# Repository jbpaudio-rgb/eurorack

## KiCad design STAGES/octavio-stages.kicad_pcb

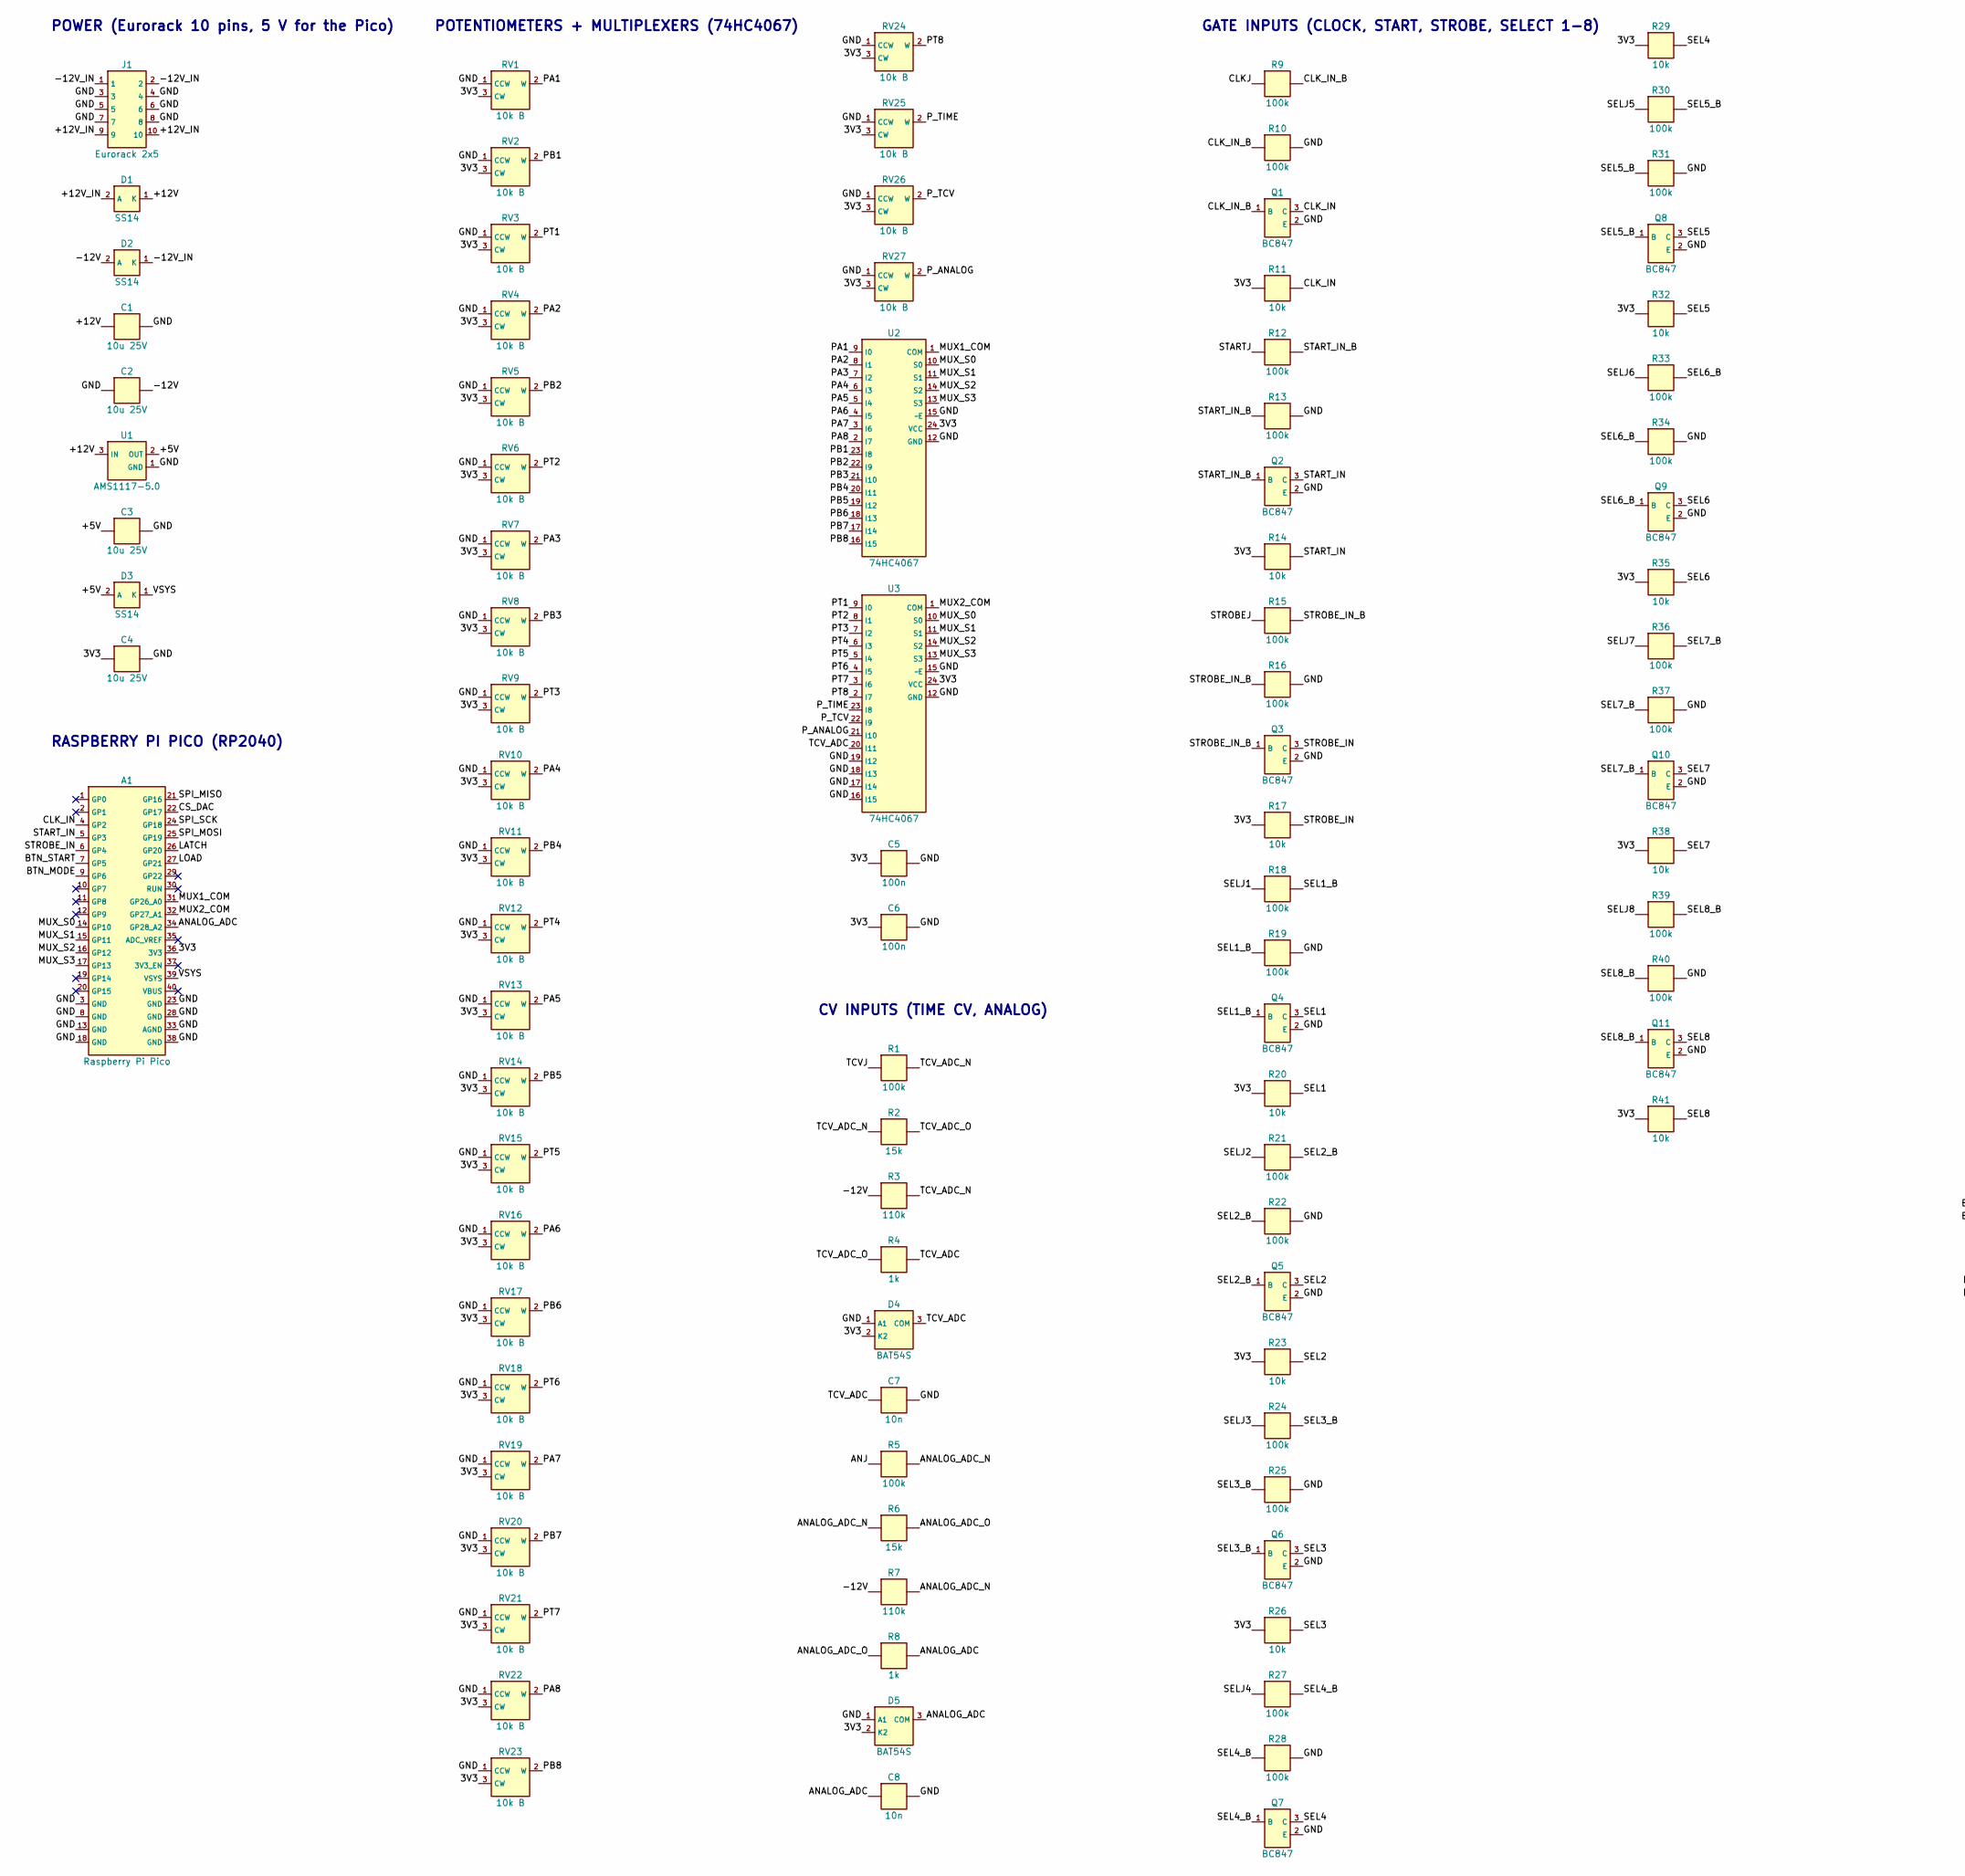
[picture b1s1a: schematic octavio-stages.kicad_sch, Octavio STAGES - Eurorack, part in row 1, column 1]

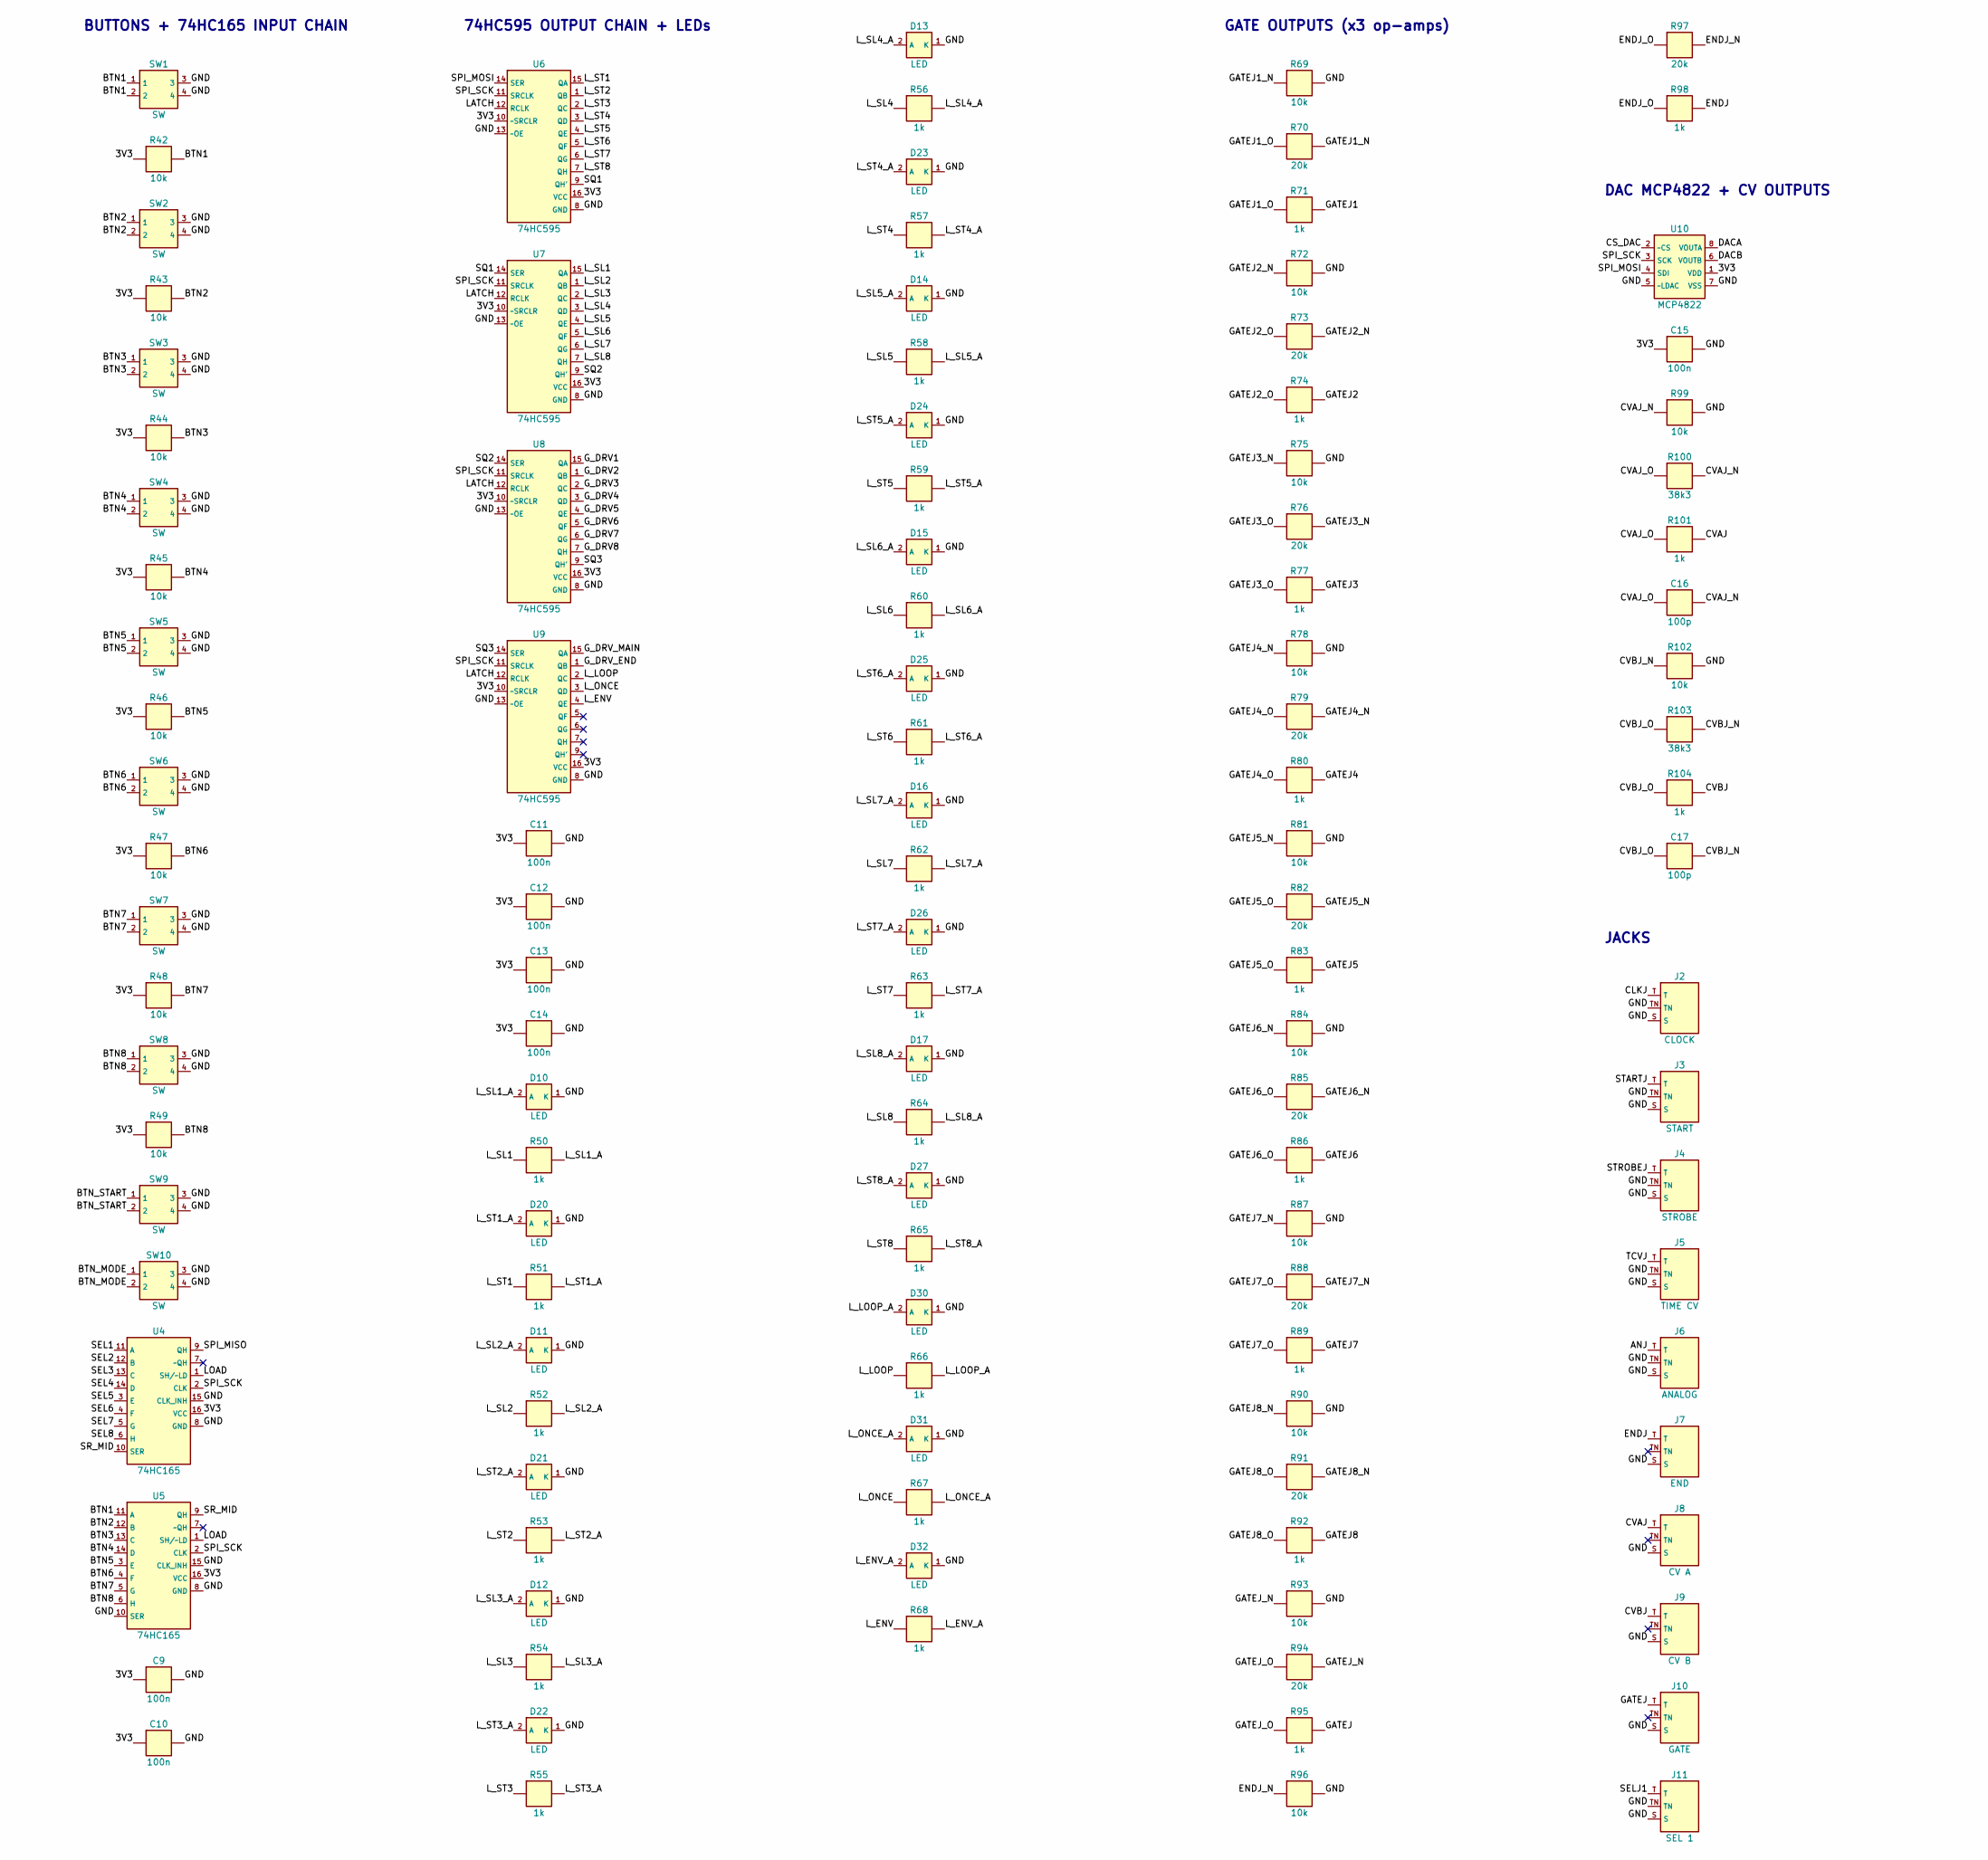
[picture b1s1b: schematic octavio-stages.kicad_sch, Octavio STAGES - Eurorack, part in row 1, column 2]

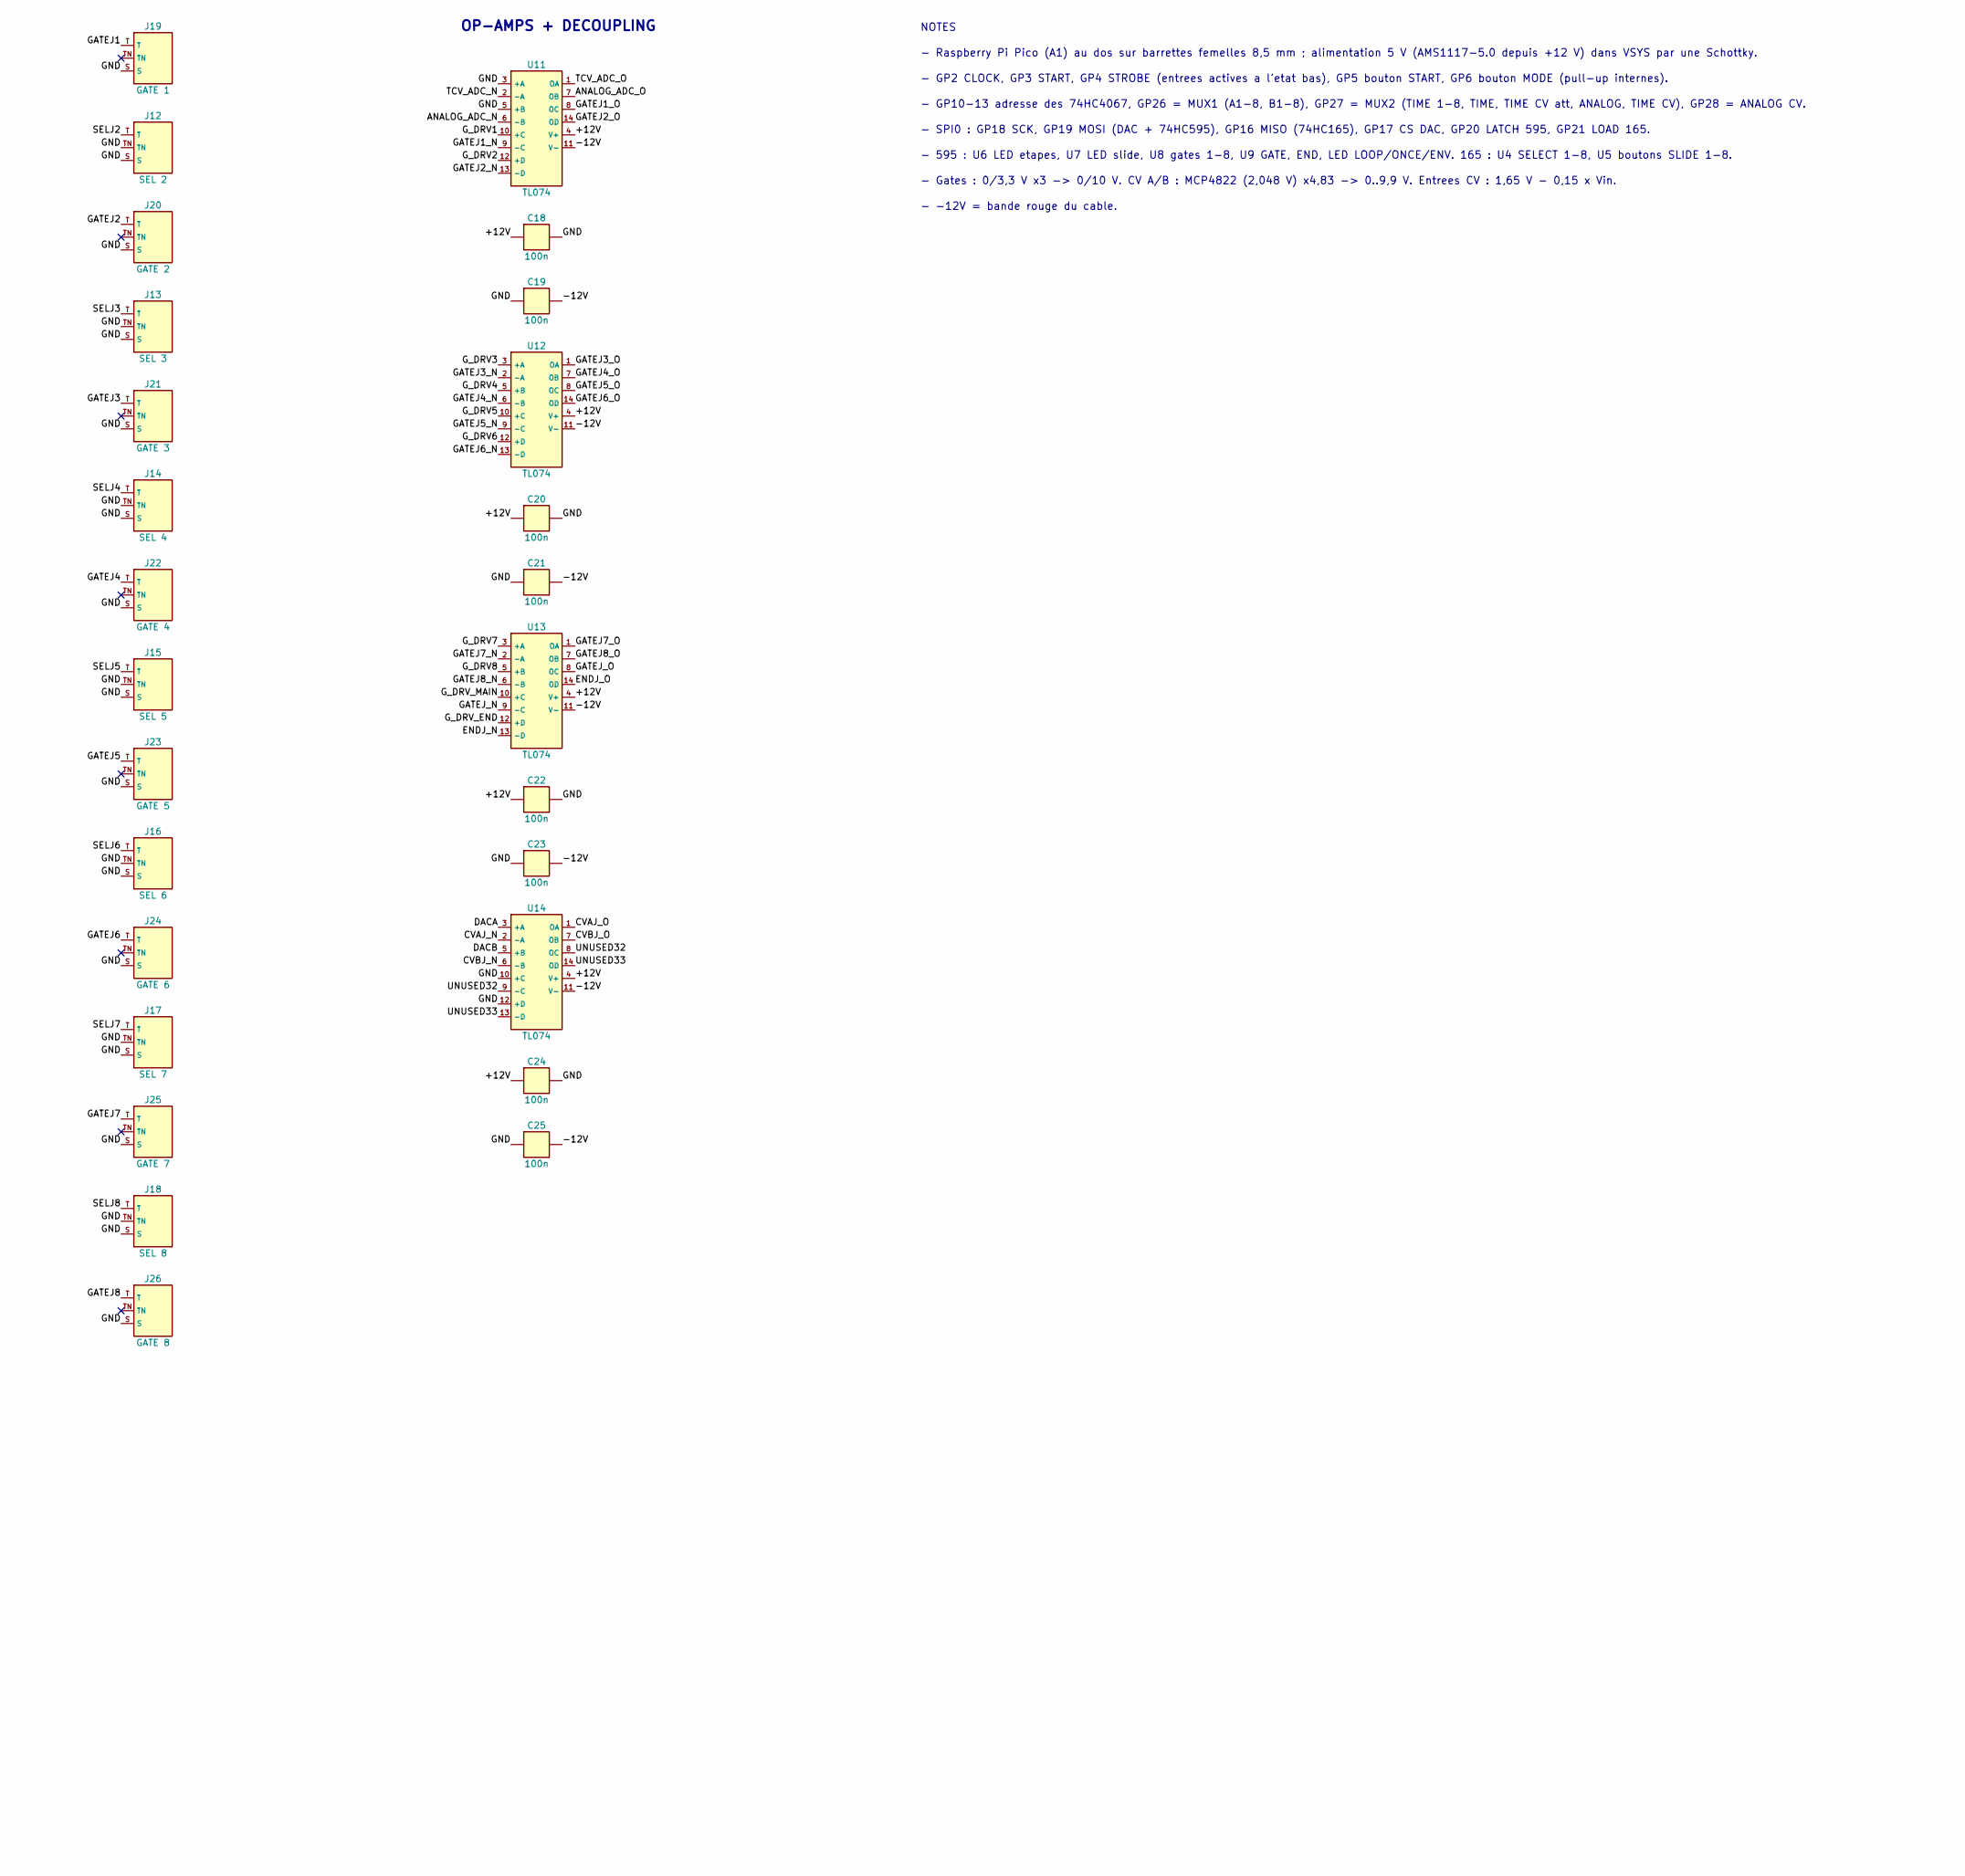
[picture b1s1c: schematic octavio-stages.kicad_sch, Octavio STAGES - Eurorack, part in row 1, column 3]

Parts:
A1: Raspberry Pi Pico; RaspberryPi_Pico_Headers; MPN Raspberry Pi Pico (RP2040) sur 2 barret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
C1, C2, C3: 10u 25V; C_1206_3216Metric; MPN X5R/X7R 1206
C4: 10u 25V; C_1206_3216Metric; MPN X5R/X7R 1206 (3,3 V des potentiomètres)
C5, C6, C9, C10, C11, C12, C13, C14, C15, C18, C19, C20, C21, C22, C23, C24, C25: 100n; C_0603_1608Metric
C7, C8: 10n; C_0603_1608Metric
C16, C17: 100p; C_0603_1608Metric
D1, D2: SS14; D_SMA; MPN SS14 (40 V 1 A Schottky)
D3: SS14; D_SMA; MPN SS14 (Schottky : USB et rack peuvent êt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
D4, D5: BAT54S; SOT-23; MPN BAT54S (protection ADC)
D10, D11, D12, D13, D14, D15, D16, D17: LED; LED_D3.0mm; MPN LED 3 mm ambre (SLIDE)
D20, D21, D22, D23, D24, D25, D26, D27: LED; LED_D3.0mm; MPN LED 3 mm rouge (étape)
D30, D31, D32: LED; LED_D3.0mm; MPN LED 3 mm ambre (mode)
J1: Eurorack 2x5; IDC-Header_2x05_P2.54mm_Vertical; MPN Shrouded header 2x5 2.54 mm
J2: CLOCK; Jack_3.5mm_Thonkiconn_PJ398SM; MPN QingPu WQP-PJ301M-12 (Thonkiconn)
J3: START; Jack_3.5mm_Thonkiconn_PJ398SM; MPN QingPu WQP-PJ301M-12 (Thonkiconn)
J4: STROBE; Jack_3.5mm_Thonkiconn_PJ398SM; MPN QingPu WQP-PJ301M-12 (Thonkiconn)
J5: TIME CV; Jack_3.5mm_Thonkiconn_PJ398SM; MPN QingPu WQP-PJ301M-12 (Thonkiconn)
J6: ANALOG; Jack_3.5mm_Thonkiconn_PJ398SM; MPN QingPu WQP-PJ301M-12 (Thonkiconn)
J7: END; Jack_3.5mm_Thonkiconn_PJ398SM; MPN QingPu WQP-PJ301M-12 (Thonkiconn)
J8: CV A; Jack_3.5mm_Thonkiconn_PJ398SM; MPN QingPu WQP-PJ301M-12 (Thonkiconn)
J9: CV B; Jack_3.5mm_Thonkiconn_PJ398SM; MPN QingPu WQP-PJ301M-12 (Thonkiconn)
J10: GATE; Jack_3.5mm_Thonkiconn_PJ398SM; MPN QingPu WQP-PJ301M-12 (Thonkiconn)
J11: SEL 1; Jack_3.5mm_Thonkiconn_PJ398SM; MPN QingPu WQP-PJ301M-12 (Thonkiconn)
J12: SEL 2; Jack_3.5mm_Thonkiconn_PJ398SM; MPN QingPu WQP-PJ301M-12 (Thonkiconn)
J13: SEL 3; Jack_3.5mm_Thonkiconn_PJ398SM; MPN QingPu WQP-PJ301M-12 (Thonkiconn)
J14: SEL 4; Jack_3.5mm_Thonkiconn_PJ398SM; MPN QingPu WQP-PJ301M-12 (Thonkiconn)
J15: SEL 5; Jack_3.5mm_Thonkiconn_PJ398SM; MPN QingPu WQP-PJ301M-12 (Thonkiconn)
J16: SEL 6; Jack_3.5mm_Thonkiconn_PJ398SM; MPN QingPu WQP-PJ301M-12 (Thonkiconn)
J17: SEL 7; Jack_3.5mm_Thonkiconn_PJ398SM; MPN QingPu WQP-PJ301M-12 (Thonkiconn)
J18: SEL 8; Jack_3.5mm_Thonkiconn_PJ398SM; MPN QingPu WQP-PJ301M-12 (Thonkiconn)
J19: GATE 1; Jack_3.5mm_Thonkiconn_PJ398SM; MPN QingPu WQP-PJ301M-12 (Thonkiconn)
J20: GATE 2; Jack_3.5mm_Thonkiconn_PJ398SM; MPN QingPu WQP-PJ301M-12 (Thonkiconn)
J21: GATE 3; Jack_3.5mm_Thonkiconn_PJ398SM; MPN QingPu WQP-PJ301M-12 (Thonkiconn)
J22: GATE 4; Jack_3.5mm_Thonkiconn_PJ398SM; MPN QingPu WQP-PJ301M-12 (Thonkiconn)
J23: GATE 5; Jack_3.5mm_Thonkiconn_PJ398SM; MPN QingPu WQP-PJ301M-12 (Thonkiconn)
J24: GATE 6; Jack_3.5mm_Thonkiconn_PJ398SM; MPN QingPu WQP-PJ301M-12 (Thonkiconn)
J25: GATE 7; Jack_3.5mm_Thonkiconn_PJ398SM; MPN QingPu WQP-PJ301M-12 (Thonkiconn)
J26: GATE 8; Jack_3.5mm_Thonkiconn_PJ398SM; MPN QingPu WQP-PJ301M-12 (Thonkiconn)
Q1, Q2, Q3, Q4, Q5, Q6, Q7, Q8, Q9, Q10, Q11: BC847; SOT-23; MPN BC847C
R1, R5, R9, R10, R12, R13, R15, R16, R18, R19, R21, R22, R24, R25, R27, R28, R30, R31, R33, R34, R36, R37, R39, R40: 100k; R_0603_1608Metric
R2, R6: 15k; R_0603_1608Metric
R3, R7: 110k; R_0603_1608Metric
R4, R8, R50, R51, R52, R53, R54, R55, R56, R57, R58, R59, R60, R61, R62, R63, R64, R65, R66, R67, R68, R71, R74, R77, R80, R83, R86, R89, R92, R95, R98, R101, R104: 1k; R_0603_1608Metric
R11, R14, R17, R20, R23, R26, R29, R32, R35, R38, R41, R42, R43, R44, R45, R46, R47, R48, R49, R69, R72, R75, R78, R81, R84, R87, R90, R93, R96, R99, R102: 10k; R_0603_1608Metric
R70, R73, R76, R79, R82, R85, R88, R91, R94, R97: 20k; R_0603_1608Metric
R100, R103: 38k3; R_0603_1608Metric
RV1, RV2, RV3, RV4, RV5, RV6, RV7, RV8, RV9, RV10, RV11, RV12, RV13, RV14, RV15, RV16, RV17, RV18, RV19, RV20, RV21, RV22, RV23, RV24, RV25, RV26, RV27: 10k B; Pot_Alpha_9mm_Vertical; MPN POT-R09V-10K (9 mm vertical, B10k)
SW1, SW2, SW3, SW4, SW5, SW6, SW7, SW8, SW9, SW10: SW; Tactile_6mm_THT_Panel; MPN Bouton 6x6 mm THT à tige longue (ex. TS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
U1: AMS1117-5.0; SOT-223-3_TabPin2; MPN AMS1117-5.0 (C6187)
U2, U3: 74HC4067; SOIC-24W_7.5x15.4mm_P1.27mm; MPN CD74HC4067M96
U4, U5: 74HC165; SOIC-16_3.9x9.9mm_P1.27mm; MPN 74HC165D
U6, U7, U8, U9: 74HC595; SOIC-16_3.9x9.9mm_P1.27mm; MPN 74HC595D
U10: MCP4822; SOIC-8_3.9x4.9mm_P1.27mm; MPN MCP4822-E/SN
U11, U12, U13, U14: TL074; SOIC-14_3.9x8.7mm_P1.27mm; MPN TL074CDR

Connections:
3V3: A1.36 (3V3), C4.1, C5.1, C6.1, C9.1, C10.1, C11.1, C12.1, C13.1, C14.1, C15.1, D4.2 (K2), D5.2 (K2), R11.1, R14.1, R17.1, R20.1, R23.1, R26.1, R29.1, R32.1, R35.1, R38.1, R41.1, R42.1, R43.1, R44.1, R45.1, R46.1, R47.1, R48.1, R49.1, RV1.3 (CW), RV2.3 (CW), RV3.3 (CW), RV4.3 (CW), RV5.3 (CW), RV6.3 (CW), RV7.3 (CW), RV8.3 (CW), RV9.3 (CW), RV10.3 (CW), RV11.3 (CW), RV12.3 (CW), RV13.3 (CW), RV14.3 (CW), RV15.3 (CW), RV16.3 (CW), RV17.3 (CW), RV18.3 (CW), RV19.3 (CW), RV20.3 (CW), RV21.3 (CW), RV22.3 (CW), RV23.3 (CW), RV24.3 (CW), RV25.3 (CW), RV26.3 (CW), RV27.3 (CW), U2.24 (VCC), U3.24 (VCC), U4.16 (VCC), U5.16 (VCC), U6.10 (~SRCLR), U6.16 (VCC), U7.10 (~SRCLR), U7.16 (VCC), U8.10 (~SRCLR), U8.16 (VCC), U9.10 (~SRCLR), U9.16 (VCC), U10.1 (VDD)
+5V: C3.1, D3.2 (A), U1.2 (OUT)
+12V: C1.1, C18.1, C20.1, C22.1, C24.1, D1.1 (K), U1.3 (IN), U11.4 (V+), U12.4 (V+), U13.4 (V+), U14.4 (V+)
+12V_IN: D1.2 (A), J1.9, J1.10
-12V: C2.2, C19.2, C21.2, C23.2, C25.2, D2.2 (A), R3.1, R7.1, U11.11 (V-), U12.11 (V-), U13.11 (V-), U14.11 (V-)
-12V_IN: D2.1 (K), J1.1, J1.2
ANALOG_ADC: A1.34 (GP28_A2), C8.1, D5.3 (COM), R8.2
ANALOG_ADC_N: R5.2, R6.1, R7.2, U11.6 (-B)
ANALOG_ADC_O: R6.2, R8.1, U11.7 (OB)
ANJ: J6.T, R5.1
BTN1: R42.2, SW1.1, SW1.2, U5.11 (A)
BTN2: R43.2, SW2.1, SW2.2, U5.12 (B)
BTN3: R44.2, SW3.1, SW3.2, U5.13 (C)
BTN4: R45.2, SW4.1, SW4.2, U5.14 (D)
BTN5: R46.2, SW5.1, SW5.2, U5.3 (E)
BTN6: R47.2, SW6.1, SW6.2, U5.4 (F)
BTN7: R48.2, SW7.1, SW7.2, U5.5 (G)
BTN8: R49.2, SW8.1, SW8.2, U5.6 (H)
BTN_MODE: A1.9 (GP6), SW10.1, SW10.2
BTN_START: A1.7 (GP5), SW9.1, SW9.2
CLKJ: J2.T, R9.1
CLK_IN: A1.4 (GP2), Q1.3 (C), R11.2
CLK_IN_B: Q1.1 (B), R9.2, R10.1
CS_DAC: A1.22 (GP17), U10.2 (~CS)
CVAJ: J8.T, R101.2
CVAJ_N: C16.2, R99.1, R100.2, U14.2 (-A)
CVAJ_O: C16.1, R100.1, R101.1, U14.1 (OA)
CVBJ: J9.T, R104.2
CVBJ_N: C17.2, R102.1, R103.2, U14.6 (-B)
CVBJ_O: C17.1, R103.1, R104.1, U14.7 (OB)
DACA: U10.8 (VOUTA), U14.3 (+A)
DACB: U10.6 (VOUTB), U14.5 (+B)
ENDJ: J7.T, R98.2
ENDJ_N: R96.1, R97.2, U13.13 (-D)
ENDJ_O: R97.1, R98.1, U13.14 (OD)
GATEJ: J10.T, R95.2
GATEJ1: J19.T, R71.2
GATEJ1_N: R69.1, R70.2, U11.9 (-C)
GATEJ1_O: R70.1, R71.1, U11.8 (OC)
GATEJ2: J20.T, R74.2
GATEJ2_N: R72.1, R73.2, U11.13 (-D)
GATEJ2_O: R73.1, R74.1, U11.14 (OD)
GATEJ3: J21.T, R77.2
GATEJ3_N: R75.1, R76.2, U12.2 (-A)
GATEJ3_O: R76.1, R77.1, U12.1 (OA)
GATEJ4: J22.T, R80.2
GATEJ4_N: R78.1, R79.2, U12.6 (-B)
GATEJ4_O: R79.1, R80.1, U12.7 (OB)
GATEJ5: J23.T, R83.2
GATEJ5_N: R81.1, R82.2, U12.9 (-C)
GATEJ5_O: R82.1, R83.1, U12.8 (OC)
GATEJ6: J24.T, R86.2
GATEJ6_N: R84.1, R85.2, U12.13 (-D)
GATEJ6_O: R85.1, R86.1, U12.14 (OD)
GATEJ7: J25.T, R89.2
GATEJ7_N: R87.1, R88.2, U13.2 (-A)
GATEJ7_O: R88.1, R89.1, U13.1 (OA)
GATEJ8: J26.T, R92.2
GATEJ8_N: R90.1, R91.2, U13.6 (-B)
GATEJ8_O: R91.1, R92.1, U13.7 (OB)
GATEJ_N: R93.1, R94.2, U13.9 (-C)
GATEJ_O: R94.1, R95.1, U13.8 (OC)
GND: A1.3 (GND), A1.8 (GND), A1.13 (GND), A1.18 (GND), A1.23 (GND), A1.28 (GND), A1.33 (AGND), A1.38 (GND), C1.2, C2.1, C3.2, C4.2, C5.2, C6.2, C7.2, C8.2, C9.2, C10.2, C11.2, C12.2, C13.2, C14.2, C15.2, C18.2, C19.1, C20.2, C21.1, C22.2, C23.1, C24.2, C25.1, D4.1 (A1), D5.1 (A1), D10.1 (K), D11.1 (K), D12.1 (K), D13.1 (K), D14.1 (K), D15.1 (K), D16.1 (K), D17.1 (K), D20.1 (K), D21.1 (K), D22.1 (K), D23.1 (K), D24.1 (K), D25.1 (K), D26.1 (K), D27.1 (K), D30.1 (K), D31.1 (K), D32.1 (K), J1.3, J1.4, J1.5, J1.6, J1.7, J1.8, J2.S, J2.TN, J3.S, J3.TN, J4.S, J4.TN, J5.S, J5.TN, J6.S, J6.TN, J7.S, J8.S, J9.S, J10.S, J11.S, J11.TN, J12.S, J12.TN, J13.S, J13.TN, J14.S, J14.TN, J15.S, J15.TN, J16.S, J16.TN, J17.S, J17.TN, J18.S, J18.TN, J19.S, J20.S, J21.S, J22.S, J23.S, J24.S, J25.S, J26.S, Q1.2 (E), Q2.2 (E), Q3.2 (E), Q4.2 (E), Q5.2 (E), Q6.2 (E), Q7.2 (E), Q8.2 (E), Q9.2 (E), Q10.2 (E), Q11.2 (E), R10.2, R13.2, R16.2, R19.2, R22.2, R25.2, R28.2, R31.2, R34.2, R37.2, R40.2, R69.2, R72.2, R75.2, R78.2, R81.2, R84.2, R87.2, R90.2, R93.2, R96.2, R99.2, R102.2, RV1.1 (CCW), RV2.1 (CCW), RV3.1 (CCW), RV4.1 (CCW), RV5.1 (CCW), RV6.1 (CCW), RV7.1 (CCW), RV8.1 (CCW), RV9.1 (CCW), RV10.1 (CCW), RV11.1 (CCW), RV12.1 (CCW), RV13.1 (CCW), RV14.1 (CCW), RV15.1 (CCW), RV16.1 (CCW), RV17.1 (CCW), RV18.1 (CCW), RV19.1 (CCW), RV20.1 (CCW), RV21.1 (CCW), RV22.1 (CCW), RV23.1 (CCW), RV24.1 (CCW), RV25.1 (CCW), RV26.1 (CCW), RV27.1 (CCW), SW1.3, SW1.4, SW2.3, SW2.4, SW3.3, SW3.4, SW4.3, SW4.4, SW5.3, SW5.4, SW6.3, SW6.4, SW7.3, SW7.4, SW8.3, SW8.4, SW9.3, SW9.4, SW10.3, SW10.4, U1.1 (GND), U2.12 (GND), U2.15 (~E), U3.12 (GND), U3.15 (~E), U3.16 (I15), U3.17 (I14), U3.18 (I13), U3.19 (I12), U4.8 (GND), U4.15 (CLK_INH), U5.8 (GND), U5.10 (SER), U5.15 (CLK_INH), U6.8 (GND), U6.13 (~OE), U7.8 (GND), U7.13 (~OE), U8.8 (GND), U8.13 (~OE), U9.8 (GND), U9.13 (~OE), U10.5 (~LDAC), U10.7 (VSS), U11.3 (+A), U11.5 (+B), U14.10 (+C), U14.12 (+D)
G_DRV1: U8.15 (QA), U11.10 (+C)
G_DRV2: U8.1 (QB), U11.12 (+D)
G_DRV3: U8.2 (QC), U12.3 (+A)
G_DRV4: U8.3 (QD), U12.5 (+B)
G_DRV5: U8.4 (QE), U12.10 (+C)
G_DRV6: U8.5 (QF), U12.12 (+D)
G_DRV7: U8.6 (QG), U13.3 (+A)
G_DRV8: U8.7 (QH), U13.5 (+B)
G_DRV_END: U9.1 (QB), U13.12 (+D)
G_DRV_MAIN: U9.15 (QA), U13.10 (+C)
LATCH: A1.26 (GP20), U6.12 (RCLK), U7.12 (RCLK), U8.12 (RCLK), U9.12 (RCLK)
LOAD: A1.27 (GP21), U4.1 (SH/~LD), U5.1 (SH/~LD)
L_ENV: R68.1, U9.4 (QE)
L_ENV_A: D32.2 (A), R68.2
L_LOOP: R66.1, U9.2 (QC)
L_LOOP_A: D30.2 (A), R66.2
L_ONCE: R67.1, U9.3 (QD)
L_ONCE_A: D31.2 (A), R67.2
L_SL1: R50.1, U7.15 (QA)
L_SL1_A: D10.2 (A), R50.2
L_SL2: R52.1, U7.1 (QB)
L_SL2_A: D11.2 (A), R52.2
L_SL3: R54.1, U7.2 (QC)
L_SL3_A: D12.2 (A), R54.2
L_SL4: R56.1, U7.3 (QD)
L_SL4_A: D13.2 (A), R56.2
L_SL5: R58.1, U7.4 (QE)
L_SL5_A: D14.2 (A), R58.2
L_SL6: R60.1, U7.5 (QF)
L_SL6_A: D15.2 (A), R60.2
L_SL7: R62.1, U7.6 (QG)
L_SL7_A: D16.2 (A), R62.2
L_SL8: R64.1, U7.7 (QH)
L_SL8_A: D17.2 (A), R64.2
L_ST1: R51.1, U6.15 (QA)
L_ST1_A: D20.2 (A), R51.2
L_ST2: R53.1, U6.1 (QB)
L_ST2_A: D21.2 (A), R53.2
L_ST3: R55.1, U6.2 (QC)
L_ST3_A: D22.2 (A), R55.2
L_ST4: R57.1, U6.3 (QD)
L_ST4_A: D23.2 (A), R57.2
L_ST5: R59.1, U6.4 (QE)
L_ST5_A: D24.2 (A), R59.2
L_ST6: R61.1, U6.5 (QF)
L_ST6_A: D25.2 (A), R61.2
L_ST7: R63.1, U6.6 (QG)
L_ST7_A: D26.2 (A), R63.2
L_ST8: R65.1, U6.7 (QH)
L_ST8_A: D27.2 (A), R65.2
MUX1_COM: A1.31 (GP26_A0), U2.1 (COM)
MUX2_COM: A1.32 (GP27_A1), U3.1 (COM)
MUX_S0: A1.14 (GP10), U2.10 (S0), U3.10 (S0)
MUX_S1: A1.15 (GP11), U2.11 (S1), U3.11 (S1)
MUX_S2: A1.16 (GP12), U2.14 (S2), U3.14 (S2)
MUX_S3: A1.17 (GP13), U2.13 (S3), U3.13 (S3)
PA1: RV1.2 (W), U2.9 (I0)
PA2: RV4.2 (W), U2.8 (I1)
PA3: RV7.2 (W), U2.7 (I2)
PA4: RV10.2 (W), U2.6 (I3)
PA5: RV13.2 (W), U2.5 (I4)
PA6: RV16.2 (W), U2.4 (I5)
PA7: RV19.2 (W), U2.3 (I6)
PA8: RV22.2 (W), U2.2 (I7)
PB1: RV2.2 (W), U2.23 (I8)
PB2: RV5.2 (W), U2.22 (I9)
PB3: RV8.2 (W), U2.21 (I10)
PB4: RV11.2 (W), U2.20 (I11)
PB5: RV14.2 (W), U2.19 (I12)
PB6: RV17.2 (W), U2.18 (I13)
PB7: RV20.2 (W), U2.17 (I14)
PB8: RV23.2 (W), U2.16 (I15)
PT1: RV3.2 (W), U3.9 (I0)
PT2: RV6.2 (W), U3.8 (I1)
PT3: RV9.2 (W), U3.7 (I2)
PT4: RV12.2 (W), U3.6 (I3)
PT5: RV15.2 (W), U3.5 (I4)
PT6: RV18.2 (W), U3.4 (I5)
PT7: RV21.2 (W), U3.3 (I6)
PT8: RV24.2 (W), U3.2 (I7)
P_ANALOG: RV27.2 (W), U3.21 (I10)
P_TCV: RV26.2 (W), U3.22 (I9)
P_TIME: RV25.2 (W), U3.23 (I8)
SEL1: Q4.3 (C), R20.2, U4.11 (A)
SEL1_B: Q4.1 (B), R18.2, R19.1
SEL2: Q5.3 (C), R23.2, U4.12 (B)
SEL2_B: Q5.1 (B), R21.2, R22.1
SEL3: Q6.3 (C), R26.2, U4.13 (C)
SEL3_B: Q6.1 (B), R24.2, R25.1
SEL4: Q7.3 (C), R29.2, U4.14 (D)
SEL4_B: Q7.1 (B), R27.2, R28.1
SEL5: Q8.3 (C), R32.2, U4.3 (E)
SEL5_B: Q8.1 (B), R30.2, R31.1
SEL6: Q9.3 (C), R35.2, U4.4 (F)
SEL6_B: Q9.1 (B), R33.2, R34.1
SEL7: Q10.3 (C), R38.2, U4.5 (G)
SEL7_B: Q10.1 (B), R36.2, R37.1
SEL8: Q11.3 (C), R41.2, U4.6 (H)
SEL8_B: Q11.1 (B), R39.2, R40.1
SELJ1: J11.T, R18.1
SELJ2: J12.T, R21.1
SELJ3: J13.T, R24.1
SELJ4: J14.T, R27.1
SELJ5: J15.T, R30.1
SELJ6: J16.T, R33.1
SELJ7: J17.T, R36.1
SELJ8: J18.T, R39.1
SPI_MISO: A1.21 (GP16), U4.9 (QH)
SPI_MOSI: A1.25 (GP19), U6.14 (SER), U10.4 (SDI)
SPI_SCK: A1.24 (GP18), U4.2 (CLK), U5.2 (CLK), U6.11 (SRCLK), U7.11 (SRCLK), U8.11 (SRCLK), U9.11 (SRCLK), U10.3 (SCK)
SQ1: U6.9 (QH'), U7.14 (SER)
SQ2: U7.9 (QH'), U8.14 (SER)
SQ3: U8.9 (QH'), U9.14 (SER)
SR_MID: U4.10 (SER), U5.9 (QH)
STARTJ: J3.T, R12.1
START_IN: A1.5 (GP3), Q2.3 (C), R14.2
START_IN_B: Q2.1 (B), R12.2, R13.1
STROBEJ: J4.T, R15.1
STROBE_IN: A1.6 (GP4), Q3.3 (C), R17.2
STROBE_IN_B: Q3.1 (B), R15.2, R16.1
TCVJ: J5.T, R1.1
TCV_ADC: C7.1, D4.3 (COM), R4.2, U3.20 (I11)
TCV_ADC_N: R1.2, R2.1, R3.2, U11.2 (-A)
TCV_ADC_O: R2.2, R4.1, U11.1 (OA)
UNUSED32: U14.8 (OC), U14.9 (-C)
UNUSED33: U14.13 (-D), U14.14 (OD)
VSYS: A1.39 (VSYS), D3.1 (K)

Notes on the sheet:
POWER (Eurorack 10 pins, 5 V for the Pico)
RASPBERRY PI PICO (RP2040)
POTENTIOMETERS + MULTIPLEXERS (74HC4067)
CV INPUTS (TIME CV, ANALOG)
GATE INPUTS (CLOCK, START, STROBE, SELECT 1-8)
BUTTONS + 74HC165 INPUT CHAIN
74HC595 OUTPUT CHAIN + LEDs
GATE OUTPUTS (x3 op-amps)
DAC MCP4822 + CV OUTPUTS
JACKS
OP-AMPS + DECOUPLING
NOTES
- Raspberry Pi Pico (A1) au dos sur barrettes femelles 8,5 mm ; alimentation 5 V (AMS1117-5.0 depuis +12 V) dans VSYS par une Schottky.
- GP2 CLOCK, GP3 START, GP4 STROBE (entrees actives a l'etat bas), GP5 bouton START, GP6 bouton MODE (pull-up internes).
- GP10-13 adresse des 74HC4067, GP26 = MUX1 (A1-8, B1-8), GP27 = MUX2 (TIME 1-8, TIME, TIME CV att, ANALOG, TIME CV), GP28 = ANALOG CV.
- SPI0 : GP18 SCK, GP19 MOSI (DAC + 74HC595), GP16 MISO (74HC165), GP17 CS DAC, GP20 LATCH 595, GP21 LOAD 165.
- 595 : U6 LED etapes, U7 LED slide, U8 gates 1-8, U9 GATE, END, LED LOOP/ONCE/ENV. 165 : U4 SELECT 1-8, U5 boutons SLIDE 1-8.
- Gates : 0/3,3 V x3 -> 0/10 V. CV A/B : MCP4822 (2,048 V) x4,83 -> 0..9,9 V. Entrees CV : 1,65 V - 0,15 x Vin.
- -12V = bande rouge du cable.
